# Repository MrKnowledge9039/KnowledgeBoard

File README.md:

# KnowledgeBoard
 Hi! This is my submission for hackpad as part of stardance program! This was made for Hackpad v5 as part of stardance mission.

## Overview
 My very first hardware project: My own Macropad called KnowledgeBoard (I know very creative), completely designed by me, with 3x3 Keys, each with a SK6812 MINI-E and 2 Rotary Encoders as well as KMK firmware. I made it because I like learning new things. Multiple times I thought macro board would be very useful but I always worked around it instead of building one. And with the opportunity of Hackpad I wanted to try to build a macroboard that suits my needs. It should be compact, simple and at the same time versatile for different jobs like replacing a Streamdeck and improving the workflow with Krita or DMXC.

## PCB
 Here are pictures of my PCB:

| **Schematic** | **PCB** |
|---------------|---------|
|||

## CAD
The Case Top and Bottom were designed using onshape. It helped that I had some experience in with 3D-Design. It was compared to that because I only used Extrude nothing complicated. Assembled are the separate case parts through screws.

## Firmware

The firmware is KMK, because it seemed easier for this project then QMK and is pretty small but has every feature the board uses and supports multiple layers.

## Notes
Making the pad was great and I will definitely progress doing also hardware projects. The Hackpad is a great starting point to get into this PCB/3D-Design.

## BOM
- 1 SEEEDUINO XIAO RP2040
- 9x MX-Style switches
- 9x white blank DSA keycaps(I try to replace them with frosted ones)
- 11x 1N4148 diodes
- 9x SK6812-MINI-E LED
- 2x EC11 Rotary encoders
- 4x M3x16mm screws
- 4x M3x16mm heatset inserts

## License
 CC-BY-SA

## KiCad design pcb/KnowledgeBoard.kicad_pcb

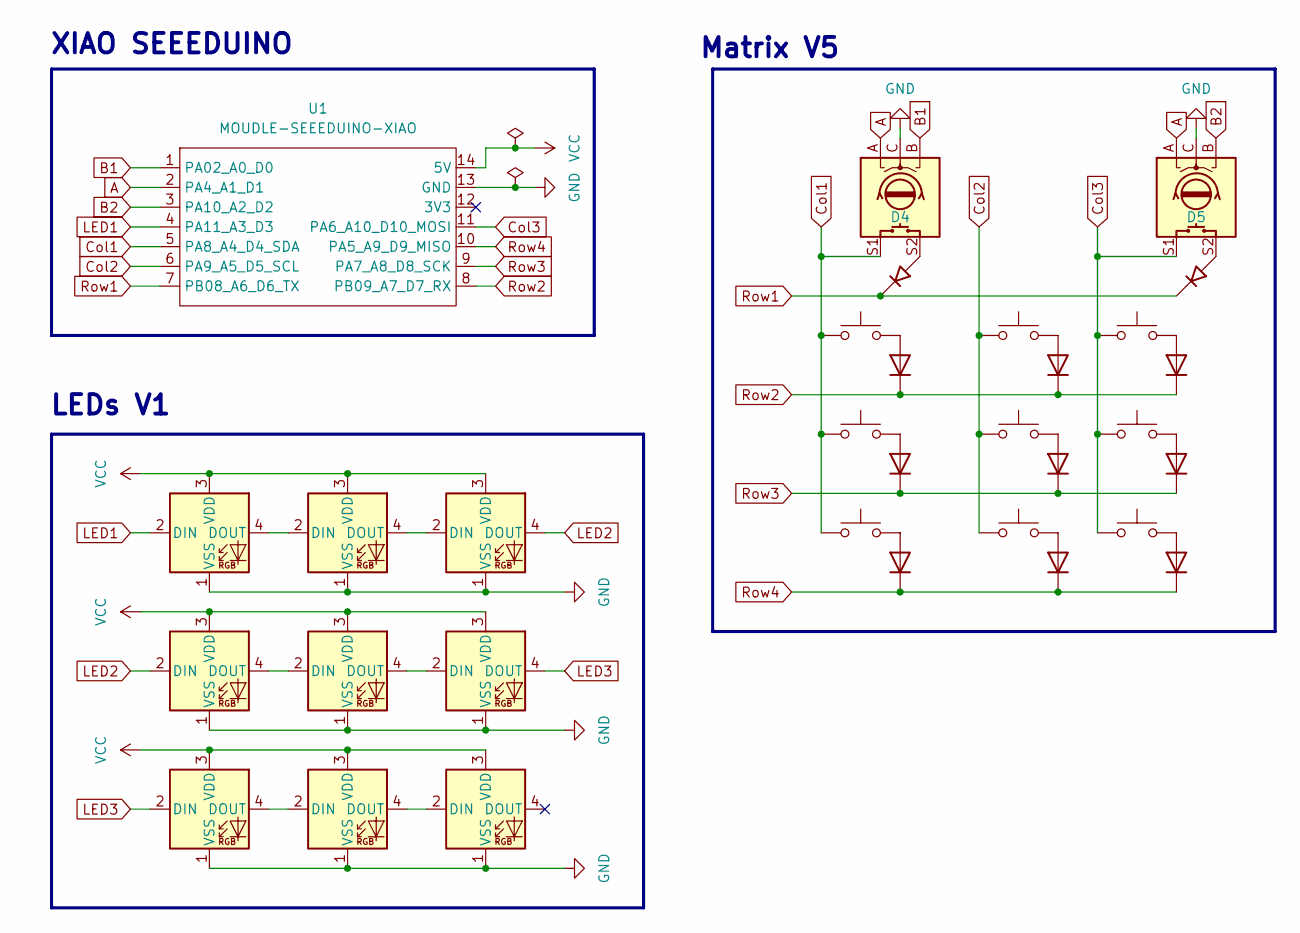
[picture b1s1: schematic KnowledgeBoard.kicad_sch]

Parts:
D1, D2, D3, D6, D7, D8, D12, D13, D14: SK6812MINI-E; SK6812MINI-E_fixed
D4, D5: D_45deg; D_DO-35_SOD27_P7.62mm_Horizontal
D9, D10, D11, D15, D16, D17, D18, D19, D20: 1N4148; D_DO-35_SOD27_P7.62mm_Horizontal
SW1, SW2: RotaryEncoder_Switch; RotaryEncoder_Alps_EC11E-Switch_Vertical_H20mm
SW3, SW4, SW5, SW6, SW7, SW8, SW9, SW10, SW11: SW_Push; SW_Cherry_MX_1.00u_PCB
U1: MOUDLE-SEEEDUINO-XIAO; XIAO-Generic-Hybrid-14P-2.54-21X17.8MM

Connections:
A: SW1.A, SW2.A, U1.2 (PA4_A1_D1)
B1: SW1.B, U1.1 (PA02_A0_D0)
B2: SW2.B, U1.3 (PA10_A2_D2)
Col1: SW1.S1, SW3.1, SW6.1, SW9.1, U1.5 (PA8_A4_D4_SDA)
Col2: SW4.1, SW7.1, SW10.1, U1.6 (PA9_A5_D5_SCL)
Col3: SW2.S1, SW5.1, SW8.1, SW11.1, U1.11 (PA6_A10_D10_MOSI)
GND: D1.1 (VSS), D2.1 (VSS), D3.1 (VSS), D6.1 (VSS), D7.1 (VSS), D8.1 (VSS), D12.1 (VSS), D13.1 (VSS), D14.1 (VSS), SW1.C, SW2.C, U1.13 (GND)
LED1: D1.2 (DIN), U1.4 (PA11_A3_D3)
LED2: D3.4 (DOUT), D6.2 (DIN)
LED3: D8.4 (DOUT), D12.2 (DIN)
unnamed: D1.4 (DOUT), D2.2 (DIN)
unnamed: D2.4 (DOUT), D3.2 (DIN)
unnamed: D4.2 (A), SW1.S2
unnamed: D5.2 (A), SW2.S2
unnamed: D6.4 (DOUT), D7.2 (DIN)
unnamed: D7.4 (DOUT), D8.2 (DIN)
unnamed: D9.2 (A), SW3.2
unnamed: D10.2 (A), SW4.2
unnamed: D11.2 (A), SW5.2
unnamed: D12.4 (DOUT), D13.2 (DIN)
unnamed: D13.4 (DOUT), D14.2 (DIN)
unnamed: D15.2 (A), SW6.2
unnamed: D16.2 (A), SW7.2
unnamed: D17.2 (A), SW8.2
unnamed: D18.2 (A), SW9.2
unnamed: D19.2 (A), SW10.2
unnamed: D20.2 (A), SW11.2
Row1: D4.1 (K), D5.1 (K), U1.7 (PB08_A6_D6_TX)
Row2: D9.1 (K), D10.1 (K), D11.1 (K), U1.8 (PB09_A7_D7_RX)
Row3: D15.1 (K), D16.1 (K), D17.1 (K), U1.9 (PA7_A8_D8_SCK)
Row4: D18.1 (K), D19.1 (K), D20.1 (K), U1.10 (PA5_A9_D9_MISO)
VCC: D1.3 (VDD), D2.3 (VDD), D3.3 (VDD), D6.3 (VDD), D7.3 (VDD), D8.3 (VDD), D12.3 (VDD), D13.3 (VDD), D14.3 (VDD), U1.14 (5V)

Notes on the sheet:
Matrix V5
XIAO SEEEDUINO
LEDs V1

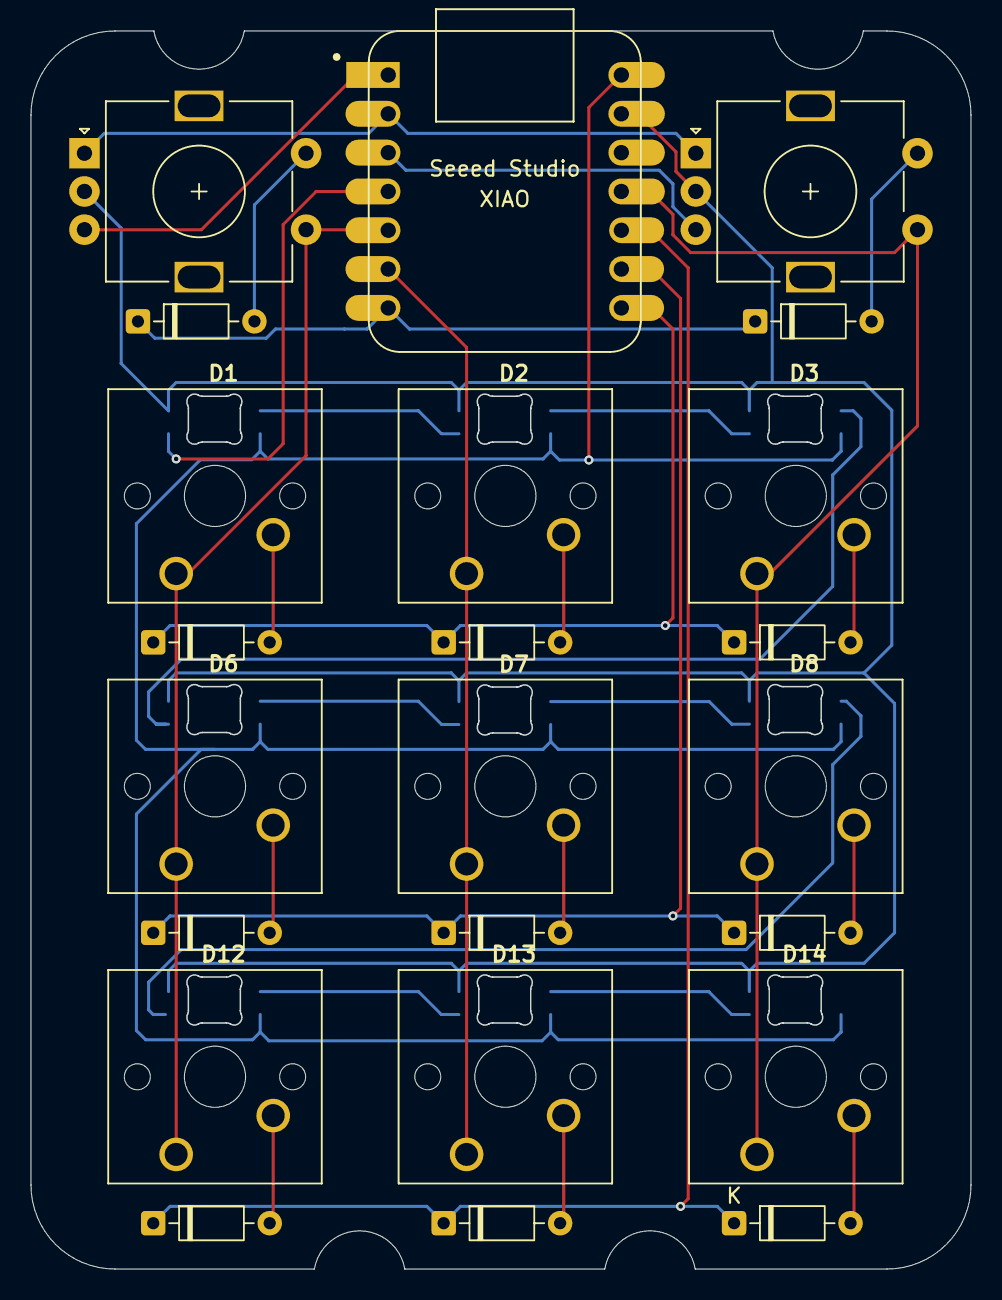
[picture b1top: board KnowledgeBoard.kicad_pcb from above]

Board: 2 copper layers, 61.5 x 81.0 mm, 32 parts (0 on the bottom side), 32 nets.

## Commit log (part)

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2026-06-29 Add initial journal entry for KiCAD exploration
    Start of the journal and first entry to KiCAD and starting MyHackpad Design
